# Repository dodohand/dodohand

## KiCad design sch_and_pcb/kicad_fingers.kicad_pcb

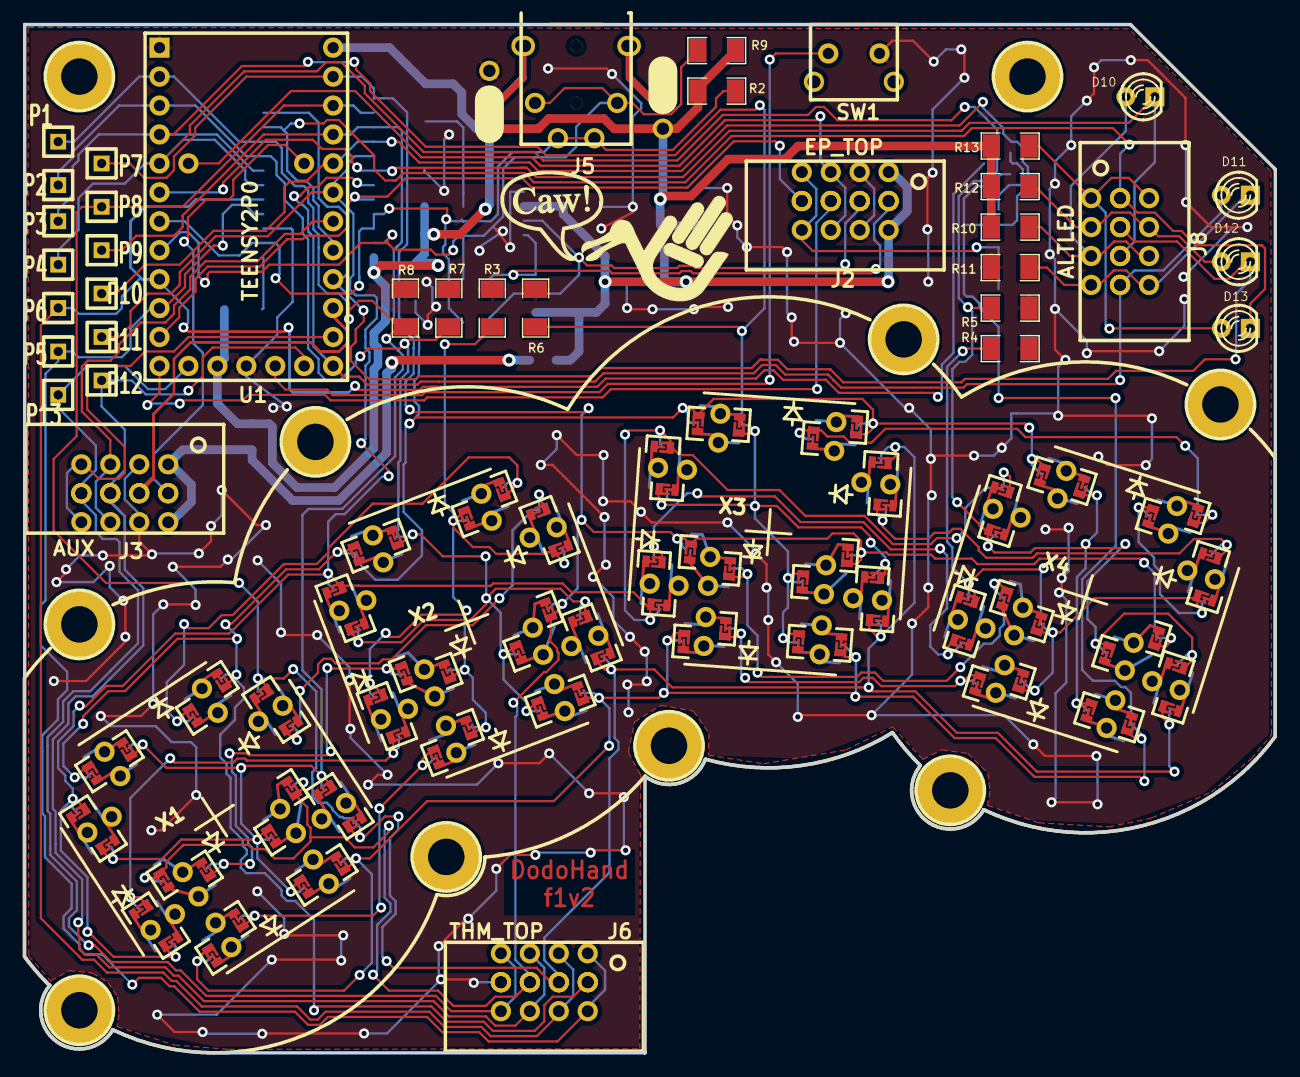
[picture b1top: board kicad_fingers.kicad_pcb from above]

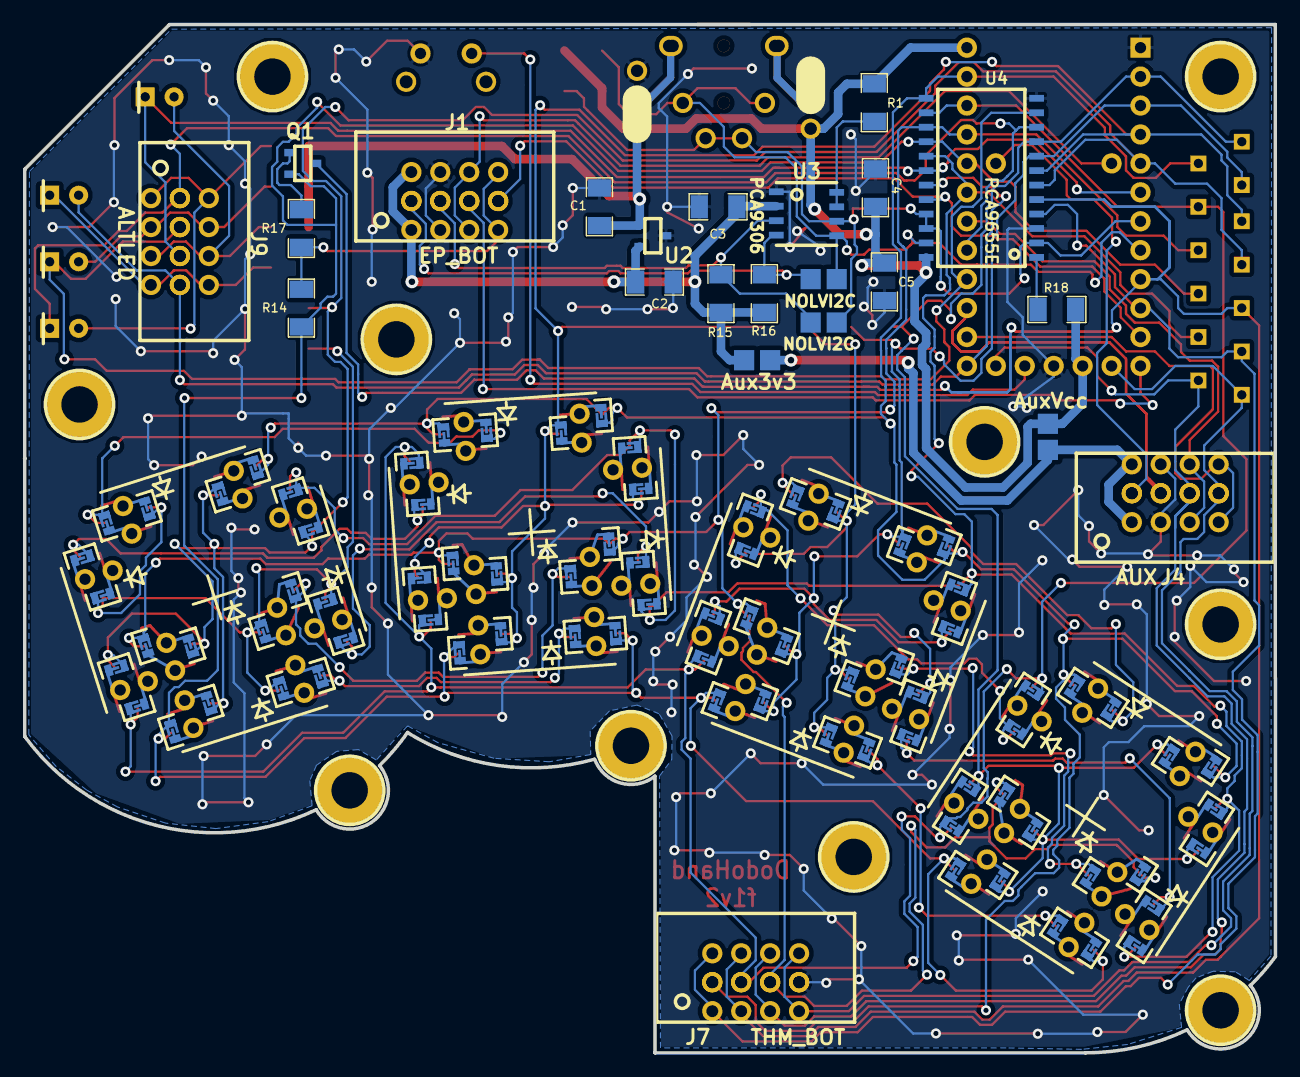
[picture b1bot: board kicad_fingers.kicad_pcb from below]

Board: 2 copper layers, 109.8 x 90.3 mm, 73 parts (23 on the bottom side), 53 nets.

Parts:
B1: AuxVcc; SOLDER_BR
B2: Aux3v3; SOLDER_BR
B3, B4: NOLVI2C; SOLDER_BR
C1: 4.7; SM1206
C2: 4.7uF; SM1206
C3, C4, C5: 0.1uF; SM1206
D10, D11, D12, D13: LED; LED-3MM-DH
J1: EP_BOT; pth_8_hdr
J2: EP_TOP; pth_8_hdr
J3, J4: AUX; pth_8_hdr
J5: SJ-43514
J6: THM_TOP; pth_8_hdr
J7: THM_BOT; pth_8_hdr
J8, J9: ALTLED; pth_8_hdr
M3_Mounting_Hole, M3_Mounting_Hole#2, M3_Mounting_Hole#3, M3_Mounting_Hole#4, M3_Mounting_Hole#5, M3_Mounting_Hole#6, M3_Mounting_Hole#7, M3_Mounting_Hole#8, M3_Mounting_Hole#9, M3_Mounting_Hole#10: VAL**; M3_Mounting_Hole
P1, P2, P3, P4, P5, P6, P7, P8, P9, P10, P11, P12, P13: TST; SIL-1
Q1: PNP_KSA1298; SOT23
R1: 200k; SM1206
R2, R9, R15, R16: 2.2k; SM1206
R3, R4: 470; SM1206
R5, R6, R7, R8: 2.49k; SM1206
R10, R11, R12, R13: 1k; SM1206
R14, R17: 5k; SM1206
R18: 10k; SM1206
SW1: SPST; PTS645V
U1: TEENSY2P0; TEENSY2p0
U2: LIN_REG; SOT23
U3: PCA9306; SO8
U4: PCA9655E; SOIC24_PCA9655E
X1, X2, X3, X4: RF5S; rf5s

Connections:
+3.3V: B2.1, C2.1, C3.2, J1.2, J2.2, R15.1, R16.1, U2.2, U3.2
/AREF: J3.2, J4.2, U1.AREF
/B4: J3.4, J4.4, U1.B4
/COL0: P1.1, R8.1, U1.B0, U4.9, X1.12, X1.14, X1.16, X1.18, X1.20
/COL1: P2.1, R7.1, U1.B1, U4.8, X2.12, X2.14, X2.16, X2.18, X2.20
/COL2: P3.1, R6.1, U1.B2, U4.7, X3.12, X3.14, X3.16, X3.18, X3.20
/COL3: P4.1, R5.1, U1.B3, U4.6, X4.12, X4.14, X4.16, X4.18, X4.20
/COL4: J6.4, J7.4, P6.1, Q1.3, U1.D2, U4.5
/COL5: J6.2, J7.2, P5.1, U1.D3, U4.4
/D4: J3.6, J4.6, J6.6, J7.6, P12.1, U1.D4
/D5: J3.8, J4.8, J6.8, J7.8, P13.1, U1.D5
/D7: J3.7, J4.7, U1.D7
/EPINT: J1.6, J2.6, U1.E6
/EPRST: J1.7, J2.7, U1.C6, U4.20
/EPSPARE: J1.5, J2.5, U1.C7
/EPSW: J1.8, J2.8, R14.1, R17.1
/F7: J3.5, J4.5, U1.F7
/LED_0: D13.2, J8.1, J9.1, U1.B6, U4.10
/LED_1: D12.2, J8.3, J9.3, U1.B5, U4.11
/LED_2: D10.2, J8.5, J9.5, U1.B7, U4.18
/LED_D6_3: D11.1, J8.7, J9.7, U1.D6, U4.19
/LVSCL: B4.2, J1.3, J2.3, R15.2, U3.3
/LVSDA: B3.2, J1.1, J2.1, R16.2, U3.4
/ROW0: J6.1, J7.1, P7.1, U1.F0, U4.13, X1.1, X1.11, X2.11, X3.1, X3.11, X4.11
/ROW1: J6.3, J7.3, P8.1, U1.F1, U4.14, X1.3, X1.13, X2.13, X3.3, X3.13, X4.13
/ROW2: J6.5, J7.5, P9.1, U1.F4, U4.15, X1.5, X1.15, X2.15, X3.5, X3.15, X4.15
/ROW3: P10.1, Q1.2, R14.2, U1.F5, U4.16, X1.7, X1.17, X2.17, X3.7, X3.17, X4.17
/ROW4: P11.1, U1.F6, U4.17, X1.9, X1.19, X2.19, X3.9, X3.19, X4.19
/SCL: B4.1, J5.3, R2.2, U1.D0, U3.6, U4.2, U4.21, U4.22
/SDA: B3.1, J5.2, R9.2, U1.D1, U3.5, U4.23
/TRST: SW1.1, U1.RST
GND: C1.2, C2.2, C3.1, C4.2, C5.2, J1.4, J2.4, J3.3, J4.3, J5.1, J6.7, J7.7, R3.2, R4.2, R5.2, R6.2, R7.2, R8.2, R11.2, SW1.2, U1.GND, U2.3, U3.1, U4.3, U4.12
unnamed: D10.1, J8.6, J9.6, R10.2
unnamed: D11.2, J8.8, J9.8, R11.1
unnamed: D12.1, J8.4, J9.4, R12.2
unnamed: D13.1, J8.2, J9.2, R13.2
unnamed: Q1.1, R17.2
unnamed: R1.1, U3.7, U3.8
unnamed: R3.1, X2.2, X2.4, X2.6, X2.8, X2.10
unnamed: R4.1, X4.2, X4.4, X4.6, X4.8, X4.10
unnamed: R18.2, U4.1
unnamed: X1.2, X2.1
unnamed: X1.4, X2.3
unnamed: X1.6, X2.5
unnamed: X1.8, X2.7
unnamed: X1.10, X2.9
unnamed: X3.2, X4.1
unnamed: X3.4, X4.3
unnamed: X3.6, X4.5
unnamed: X3.8, X4.7
unnamed: X3.10, X4.9
VCC: B1.1, C1.1, C4.1, C5.1, J5.4, R1.2, R2.1, R9.1, R10.1, R12.1, R13.1, R18.1, U1.Vcc, U2.1, U4.24
VCOM: B1.2, B2.2, J3.1, J4.1

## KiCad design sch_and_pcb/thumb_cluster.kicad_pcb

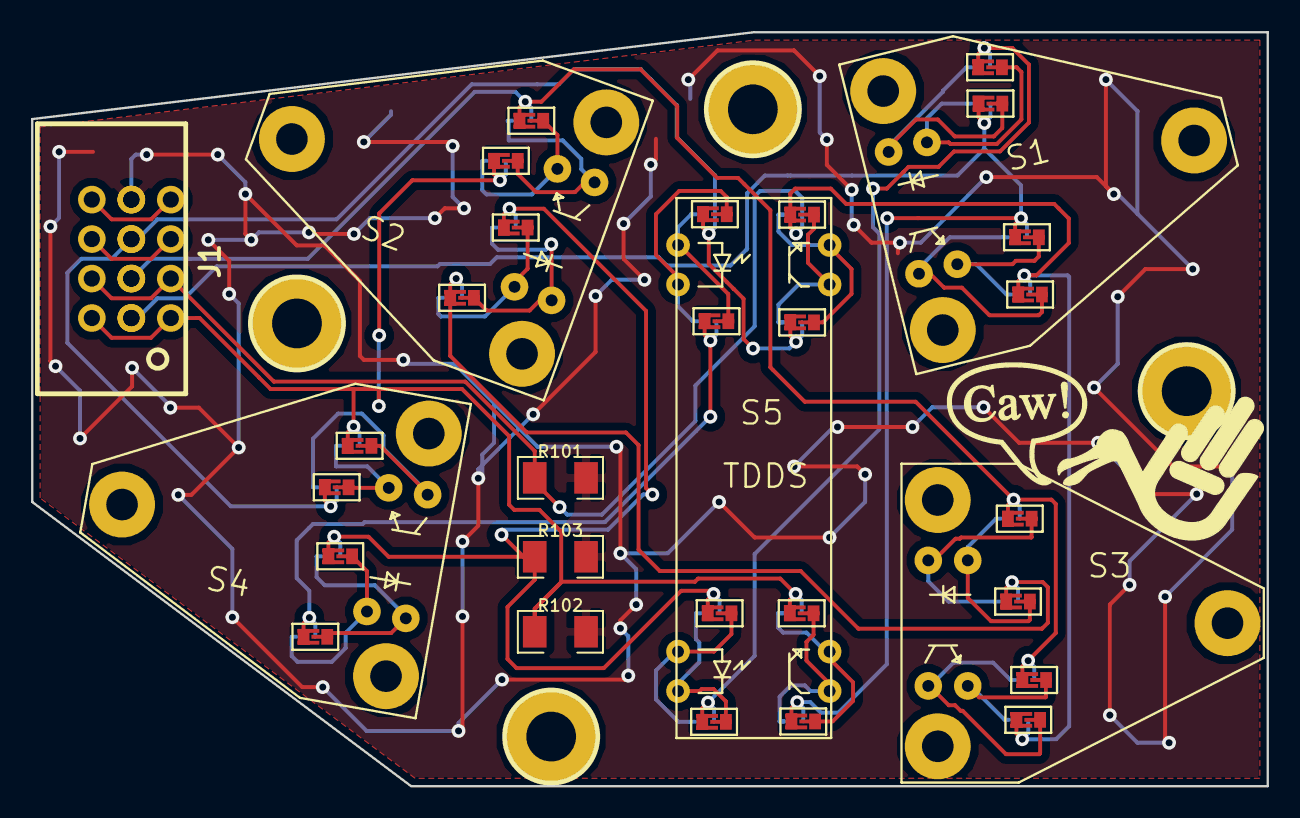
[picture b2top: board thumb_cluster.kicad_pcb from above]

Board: 2 copper layers, 79.5 x 48.5 mm, 38 parts (1 on the bottom side), 36 nets.

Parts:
J1, J2: 8PIN_CONN; pth_8_hdr
M3_Mounting_Hole, M3_Mounting_Hole#2, M3_Mounting_Hole#3, M3_Mounting_Hole#4: VAL**; M3_Mounting_Hole
R101, R102: 2.49k; SM1206
R103: 470; SM1206
S1: S1; ThumbSwitch
S2: S2; ThumbSwitch
S3: S3; ThumbSwitch
S4: S4; ThumbSwitch
S5: TDDS
SB1, SB2, SB3, SB4, SB5, SB6, SB7, SB8, SB9, SB10, SB11, SB12, SB13, SB14, SB15, SB16, SB17, SB18, SB19, SB20, SB21, SB22, SB23, SB24: 2XSSB; 2xSideSolderSwitch

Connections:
/COL4: J1.4, J2.4, R101.1, SB13.1, SB14.1, SB15.1
/COL5: J1.2, J2.2, R102.1, SB16.1, SB17.1, SB18.1
/D4: J1.6, J2.6
/D5: J1.8, J2.8
/ROW0: J1.1, J2.1, SB1.1, SB19.1, SB22.1
/ROW1: J1.3, J2.3, SB2.1, SB20.1, SB23.1
/ROW2: J1.5, J2.5, SB3.1, SB21.1, SB24.1
GND: J1.7, J2.7, R101.2, R102.2, R103.2
unnamed: R103.1, SB10.1, SB11.1, SB12.1
unnamed: S1.1, SB1.3, SB7.2
unnamed: S1.2, SB1.2, SB7.3
unnamed: S1.3, SB13.3, SB19.2
unnamed: S1.4, SB13.2, SB19.3
unnamed: S2.1, SB5.3, SB11.2
unnamed: S2.2, SB5.2, SB11.3
unnamed: S2.3, SB17.3, SB23.2
unnamed: S2.4, SB17.2, SB23.3
unnamed: S3.1, SB2.3, SB8.2
unnamed: S3.2, SB2.2, SB8.3
unnamed: S3.3, SB14.3, SB20.2
unnamed: S3.4, SB14.2, SB20.3
unnamed: S4.1, SB6.3, SB12.2
unnamed: S4.2, SB6.2, SB12.3
unnamed: S4.3, SB18.3, SB24.2
unnamed: S4.4, SB18.2, SB24.3
unnamed: S5.1, SB3.3, SB9.2
unnamed: S5.2, SB3.2, SB9.3
unnamed: S5.3, SB4.3, SB10.2
unnamed: S5.4, SB4.2, SB10.3
unnamed: S5.5, SB16.3, SB22.2
unnamed: S5.6, SB16.2, SB22.3
unnamed: S5.7, SB15.3, SB21.2
unnamed: S5.8, SB15.2, SB21.3
unnamed: SB4.1, SB7.1
unnamed: SB5.1, SB8.1
unnamed: SB6.1, SB9.1

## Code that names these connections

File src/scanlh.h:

/*
    This file is part of the DodoHand project. This project aims to create 
    an open implementation of the DataHand keyboard, capable of being created
    with commercial 3D printing services.

    Copyright (C) 2014 Scott Fohey

    This program is free software: you can redistribute it and/or modify
    it under the terms of the GNU General Public License as published by
    the Free Software Foundation, either version 3 of the License, or
    (at your option) any later version.

    This program is distributed in the hope that it will be useful,
    but WITHOUT ANY WARRANTY; without even the implied warranty of
    MERCHANTABILITY or FITNESS FOR A PARTICULAR PURPOSE.  See the
    GNU General Public License for more details.

    You should have received a copy of the GNU General Public License
    along with this program.  If not, see <http://www.gnu.org/licenses/>.
*/
#ifndef __SCANLH_H__
#define __SCANLH_H__

#include "dh_types.h"

#define LH_KB_COLS ( 6u )

/*
 * Row0 = Pin F0
 * Row1 = Pin F1
 * Row2 = Pin F4
 * Row3 = Pin F5
 * Row4 = Pin F6
 *
 * Col0 = Pin B0
 * Col1 = Pin B1
 * Col2 = Pin B2
 * Col3 = Pin B3
 * Col4 = Pin D2
 * Col5 = Pin D3
 *
 */

#define PORTF_ROW_MASK ( 0x73u )
#define PORTF_ROW_0    ( 0x01u )
#define PORTF_ROW_1    ( 0x02u )
#define PORTF_ROW_2    ( 0x10u )
#define PORTF_ROW_3    ( 0x20u )
#define PORTF_ROW_4    ( 0x40u )

#define PORTB_COL0_PIN ( 0x00u )
#define PORTB_COL1_PIN ( 0x01u )
#define PORTB_COL2_PIN ( 0x02u )
#define PORTB_COL3_PIN ( 0x03u )
#define PORTD_COL4_PIN ( 0x02u )
#define PORTD_COL5_PIN ( 0x03u )

#define COL_STAB_T_US ( 300u )

#define KB_ROWS    (5u)

extern bool lh_matrix[KB_ROWS][LH_KB_COLS];

extern void scanlh ( void );




#endif // __SCANLH_H__

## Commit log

2014-01-07 Initial import to github. Scanning of right-hand matrix working well.
2014-01-12 Added jumpers and noted standoffs in BOM. Overview added to README.
2014-01-13 led_test now also scans the left-hand matrix.
2014-01-14 first pass at a mechanical drawing for clip no. 1.
2014-01-16 .blend of Case Components
    This is a mock up of the case components.
2014-01-17 prior to redline by an M.E.
2014-01-17 clip_1_mech.dxf ready for quote.
2014-01-17 Added cross-hatch in Section A-A. Tweaked README.
2014-02-13 just starting work on thumb switches.
2014-02-16 tweaked.
2014-02-16 corrections, shoulder added.
2014-02-16 winding of polyhedron corrected thanks to Marius Kintel of OpenSCAD.
2014-02-16 blade overall structure/shape done. now need to add clip support.
2014-02-21 moving towards a final form for thumb switch rotating part.
2014-02-22 trp now shaped for clip insertion.
2014-02-22 thumb rotating part shape v 1.0
2014-02-23 started work on frame for 4-per-side thumb switches
2014-02-23 more work towards thumb frame
2014-02-23 now recognizable, significant work left to do on tf.
2014-02-25 added gussets to support side-loads.
2014-02-25 filled in area under irled holders for strength.
2014-02-26 corners of baseplate removed.
2014-02-26 retention clips added.
2014-03-02 adjusted tf dimensions towards less trp rotation.
2014-03-08 moved spline and added hole in spline to allow keycap to lock into spline.
2014-03-08 keycapbase created - can now create keycaps in Blender for easier organic shape.
2014-03-23 starting work on thumb down double-switch.
2014-03-25 further work towards the tdds.
2014-03-30 added magnet holder to one end of bar.
2014-03-31 re-wrote tdds to take advantage of symmetries.
2014-03-31 tdds switch mechanism functional. KeyCap still to be created and mounting provided.
2014-03-31 added pressure bumps to ensure IRLEDs are held firmly.
2014-09-16 added retention bumps for TDDS keycap.
2014-10-02 added tdds lifting travel stop. Also calculation for tdds keycap rotation.
2014-10-04 beginnings of tdds keycap.
2014-10-06 tdds keycap now clearanced for magnets. correctly attached to pivot.
2014-10-06 shaped the tdds keycap.
2014-10-07 tdds v.1 completed.
2014-10-07 cleanup of 5key_assy to get printable model again. (Shapeways started rejecting because of chock being small.)
2014-10-11 keycap base locking clip corrected.
2014-10-11 tweaked the docs.
2014-10-11 4 of the 5 thumb keycaps now completed.
2014-10-12 initial arrangement of thumb switches completed.
2014-10-13 tweaking of proximal, inner thumb keycap.
2014-10-14 Rearrange thumb cluster parts into tc.scad.
2014-10-14 starting work on thumb pcb
2014-10-20 starting work on thumb PCB.
2014-10-21 PCB mostly routed. Shape not yet defined.
2014-10-21 ground plane connected. silk cleanup still needed. soldermask slightly wrong on solder bridge. Needs corrected.
2014-10-22 First pass of the Thumb Cluster PCB is complete.
2014-10-23 partway done organizing model for printing.
2014-10-26 First print of thumb cluster with this version.
2014-10-29 added switch identifiers to switch matrix diagram.
2014-10-29 White background added.
2014-10-29 updated docs.
2014-11-12 notes after working with switches.
2014-11-15 Corrected TDDS footprint, had to put it into new library in new .pretty directory format.
2014-11-15 removed defective footprint from old library.
2014-11-16 added script to get relevant datasheets.
2014-11-17 correction to PNP transistor connections for easypoint switch evaluation.
2014-11-19 tweaked for new rev of compiler, and for testing of thumb in/up switch.
2014-11-24 Switch matrix corrected to show PNP for easypoint evaluation.
2015-09-18 first pass at magnet switch.
2015-09-18 reduced stress on catches during insertion of trp into frame.
2015-09-18 better stress reduction on tf catches.
2015-10-31 shrunk the height on the thumb keyswitches a bit.
2015-11-26 updated a bit of documentation.
2015-12-01 BOM updated to include thumb parts.
